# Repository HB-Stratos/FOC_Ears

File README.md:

Hi there! Since the below was written, a few more things have happened:

You can **send me your Email if you want to get involved with development** and I'll reach out. [Click Here](https://app.formbricks.com/s/cmjj02hcw36xmad01dme5074u).

Work has also started on a PCB based version. PCBs have been ordered, and may or may not have arrived in time for Congress. \
In any case, you can find all KiCad files [on the rev2 branch](https://github.com/HB-Stratos/FOC_Ears/tree/rev-2).

# FOC Ears: Dead Silent Animatronics, a Prototype

This repository documents my work to create truly silent animatronic cat ears.

The classic design using RC airplane servos is quite noisy, and I wanted to fix that to build animatronics that you can comfortably hold a conversation around.

## Table of Contents

- [FOC Ears: Dead Silent Animatronics, a Prototype](#foc-ears-dead-silent-animatronics-a-prototype)
  - [Table of Contents](#table-of-contents)
  - [Status](#status)
    - [Future Plans](#future-plans)
  - [Documentation](#documentation)
    - [System Overview](#system-overview)
      - [Components](#components)
      - [Motor Assembly](#motor-assembly)
    - [Wiring](#wiring)
    - [3D Prints and Mounting](#3d-prints-and-mounting)
    - [Build Environment Setup](#build-environment-setup)
    - [Misc. Lessons Learned](#misc-lessons-learned)
  - [Thanks](#thanks)
  - [Finally](#finally)

## Status

I managed to create a working prototype in time for GPN23. It has a rather bulky perfboard electronics package and several electronic design limitations, such as the lack of a fuse, but it held up well for the entire event. Unfortunately, my phone died between building the prototype and writing this documentation, so I have lost some work-in-progress photographs. Words and renders will have to suffice.

<details>
<summary>More Pictures (expand)</summary>

</details>

### Future Plans

I plan to develop a more robust version with a printed circuit board between the ears to house the electronics in a much neater way. I would like to eventually create a product out of this development, but even if I do, I plan to keep all design files and details open source.

## Documentation

> [!IMPORTANT] > **This is a prototype**. I am documenting this for sake of posterity. If you wish to replicate this design, you are welcome to do so. However, expect to face issues, poor design decisions and have expect to solve many stupid problems on your own. Because of this, this is not written as a tutorial, but more as an overview of what it takes. That said, I'm happy to help where I can, just leave an issue on the repo here.

With that said, lets get into it

### System Overview

#### Components

The system consists of the following components:

- An [ESP32WROOM](https://aliexpress.com/item/1005008002597306.html) micro controller <br>

- Two [SimpleFOC mini](https://docs.simplefoc.com/simplefocmini) driver boards <br>

- Two [Mitoot 2208 100kv](https://aliexpress.com/item/1005006008489660.html) Brushless Gimbal Motors <br>

- Two [MT6701qt](https://aliexpress.com/item/1005007349429583.html) Magnetic Encoders <br>

- A [BNO055](https://aliexpress.com/item/1005006770124726.html) IMU <br>

- Ears from Aliexpress. There appears to be a whole range of different style ears on Aliexpress, all following the same basic design. Look for the ears in the ~10€ price class, those will likely be extremely similar to [the ones I used](https://aliexpress.com/item/1005004647818937.html). <br>

- A generic 3.3V Regulator (must be 15V capable)
- A generic configurable USB-C PD trigger board (prototype used 15V)
- A generic USB-C PD capable Power Bank (in my case 100W 20V capable)

Total cost exluding the power bank comes out to ~53€.

Images were taken from their respective linked pages.

> [!NOTE]
> The hardware choices I made worked, but were not ideal:
>
> - The ESP32 can not be flashed without having to hold down the boot button every time
> - The Motors come with the wire through their hub, so one needs to depin the connector, pull the cable through and add the pins again.
> - The Motors are also a bit large, smaller probably works but untested.
> - The Encoder board is undocumented, had to be reverse engineered with the chip data sheet
> - The BNO055 has some hardware issues and is also discontinued, but it was the board I had laying around.

#### Motor Assembly

The motor and encoder are mounted together by a stack of parts that clamps the two to each other and the assembly to the head band using all the same screws. The magnet for the encoder is held within the hollow motor shaft by a press fit 3d printed adapter. The ears are mounted on top with two M2x6 screws through the U channel piece.

Ordinarily this wouldn't work as the holes in the motor do not match the holes in the encoder PCB. However there is nothing vital in the ares of the encoder PCB where the holes are needed, so I devised a 3d printed drilling jig to create the required holes. Of course this technique is only applicable to the exact sensor board I used.

> [!CAUTION]
> Using too long screws to clamp the motor-encoder assembly together will destroy the motor. The holes do not have a backstop, so you will penetrate the coils with the screw. You will not feel rotational resistance as this happens as you are only hitting the stator. I used M2.5x8 screws.

The ears are mounted by making a cutout in them with flush cutters to fit the U channel piece, which is then glued into place with super glue. It is vital that this cut is deeper than the u channel such that the outer edges of the ear sit as flush as possible to the head band. The U channel does not extend all the way down as it would snag on the motor cables if it did.

Additionally, for secondary motion the lower ear lobe of each ear is mounted to a slider on the head band. This causes the ear to fold on rotation, which looks much more natural than the long ear lobe swinging backwards. This however has the issue that the aliexpress ears come with thick wire in them for posing, which would prevent this motion. The solution is as simple as it is ugly: fatigue cracking the wire every 5 or so mm with pliers within the area that should bend. The slider is printed from TPU for silent motion and (surprisingly) low friction.

> [!NOTE]
> I have tried to completely remove the wire from the ears. The wire is hot glued in place within the ears in multiple places, and the fur is bonded together firmly. Even by cutting along the edge of the ear all the way around I was not able to extract the wire in the base of the ear, and said cut looked quite ugly and would have been hard to close up again. Hence I deemed it better to leave the wire in place, but fatigue crack it where necessary. A less hand-fatiguing solution is definitely needed for higher volume production though.

The ear detached from the motor, with lines highlighting roughly where I broke the internal wire. Also visible is the TPU slider, here detached from the rail.

### Wiring

PowerPoint graphic design is my passion. Not pictured are 3.3v running to all sensors, shared ground between all and a 2.2k pullup resistor between SDA and 3.3V on the BNO055. Additionally, note that I used SimpleFOC Mini 1.0 driver boards as they were easily available on Aliexpress. SimpleFOC Mini 1.1 drivers are similar, but their pin order appears to be flipped.

Here's the reverse-engineered diagram for the encoder. Also, [here's the datasheet](https://uploadcdn.oneyac.com/attachments/files/brand_pdf/magntek/F3/CA/MT6701QT-STD.pdf).

> [!NOTE]
> This encoder is supposedly capable of I2C and SSI (we use SSI), and CS would toggle between the two modes. However this would cause bad I2C writes on the shared SSI bus with CS off, which I have heard reported, but could never observe myself. I can only assume my specific board has some resistors onboard that disable I2C.

A closeup of the final breadboard. Unsurprisingly, gluing circuit boards together edge to edge did not prove to be particularly sturdy, and the design made the USB-C cable start uncomftably low. But it did work.

### 3D Prints and Mounting

This is the mount for the board, based of my earlier design of ear hook glasses clips to mount non-animatronic ears. This glasses clip is desiged for my glasses (Zenni Optical [Navy Rectangle Glasses #2018916](https://www.zennioptical.com/p/tr-rectangle-eyeglass-frames/20189/2018916) ), so if these do not also happen to be your glasses you will have to devise a custom mounting solution. I am yet to come up with a generic solution that would work with all glasses while still looking good.

Also, this piece is a royal pain to print as one might expect. The first print of it I did completed, but all five attempts to print a spare piece before the event failed.

The parts constituting one motor-encoder-ear sandwich, laid out in the orientation I printed them in.

The ear lobe slider which glides on the metal headband. It is printed from TPU for silent motion. Earlier prototypes showed that even the slightest bit of noise so close to the wearer's ear is quite annoying.

All 3d printed parts can be found in the `printed_parts` directory as STEP files, as well as the original Fusion360 source files. Do note however that the source files are a royal mess as they were created during prototyping and with exactly zero patience.

### Build Environment Setup

This project uses PlatformIO instead of the Arduino IDE as it has far superior code completion and extension support. Setting up the build environment should just be as easy as setting up PlatformIO using the [official guide](https://docs.platformio.org/en/latest/integration/ide/vscode.html#quick-start) and cloning this repository into the workspace. It will take a few minutes to load, but PlatformIO should automatically download all required frameworks and libraries as specified in the `platformio.ini` file. If this doesn't work for whatever reason, please do open an issue. Also, for some reason this was removed from the official settings, but PlatformIO does offer an "Upload and Monitor (connect to Serial Monitor immediately)" mode. You can find out how to set this up [here](https://community.platformio.org/t/shortcut-to-upload-and-monitor-task-while-also-restarting-it-if-active/18104/5).

### Misc. Lessons Learned

- If the screws clamping the encoder to the motor are not tight enough, the motor likes to shake itself to bits as it twisting against the encoder causes a feedback loop.
- If the screws clamping the encoder to the motor are too tight, they can stretch a poorly printed plastic clamp and make the mounting screws penetrate the motor core.
- Having a cheap oscilloscope ([Zoyi ZT-703S](https://aliexpress.com/item/1005006593085723.html), ~80€) was invaluable during development, you likely want one too.
- At least on my BNO055 board the I2C pullups were too weak for high frequencies, an external pullup was needed.
- Having a Dupont connector crimping tool is quite useful.
- Surprisingly, the mess of wires going from the sensors and motors to the perfboard never got tangled. Still, they're a bad design.
- Having any D term in the PID motion controllers makes the motor quite noisy.
- High loop speed of the main FOC loop is important for precise and silent control.
- Any change in loop speed also constitutes a change in optimal PID values, a fixed loop speed would be a good code design choice I did not make.
- A RP2040 has pretty low loop speed due to lack of a hardware floating point unit, not ideal for this application.
- Many in and output pins are needed to control the motors, 4 per motor driver, one per sensor plus two more sensor shared pins, plus the I2C pins for the IMU. I almost ran out of useable IO pins on the ESP32.
- Reading the IMU every loop slows the motor control loop down too much, reading the IMU every 10 ms was found to be sufficient.
- A PT1 filter element was integrated into the motor driver to limit maximum acceleration, safeguarding from a position step input being too violent.
- The clamping pieces should be printed from ASA or similar, especially during testing or with a sensor error, the motors can get quite hot.
- The metal hoop that comes with the aliexpress cat ears is bent outwards at the bottom. Bending it straight makes sliding mounts with much tighter tolerances on possible.
- Fatigue cracking the ears works, but likes to compress the fur under the pliers. Scratching it with finger nails appears to restore most of the fluff.
- Mounting the ears to my glasses proved essential. The motors are not the lightest, and with my mounting solution clipping onto my glasses and hooking behind my ears, I never feared losing the ears. I am yet to come up with a solution that would work for all glasses frames, let alone a solution for people who do not wear glasses.
- Espressif changed something in more recent versions of the framework, which broke SimpleFOC. It either doesn't compile or kernel panics. I went and found the newest version released before the latest SFOC release, which worked well. You can find the details in the platformio.ini file.
- SimpleFOC requires that PlatformIO `lib_archive = false`. If it isn't your code will compile and run, but behave weirdly in all sorts of strange ways. Be careful.
- The Motors claim they can handle 12V, but I have driven them to 20V with no issues. I just went with 15V as I didn't need the torque and it slowed the motor heating up should an ear become blocked.
- This project started with me trying to use silent stepper drivers and motors for the motion instead of FOC. However, the holding current being constantly drawn by the stepper motors made them get very hot while still lacking torque to not miss steps. Still, using TMC2209 stepper drivers might work for smaller animatronics such as blinking eyes.
- If you can't upload the code with error Access Denied, check if you have a 3D printer slicer such as Cura open. It was automatically trying to connect to all COM ports for me, blocking code uploads.

## Thanks

to everyone who helped me with this project. Especially the amazing people of the Voidstarlab and SimpleFOC discord who took their time to not only help me debug problems with my motor setup, but also with reverse engineering the Encoder PCB, debugging the IMU and many other hardware engineering issues unrelated to SFOC. This was my first true hardware engineering project. I learned a ton, and I couldn't have done it without y'all.

## Finally

Overengineer more silly projects, build cool stuff, and have fun!

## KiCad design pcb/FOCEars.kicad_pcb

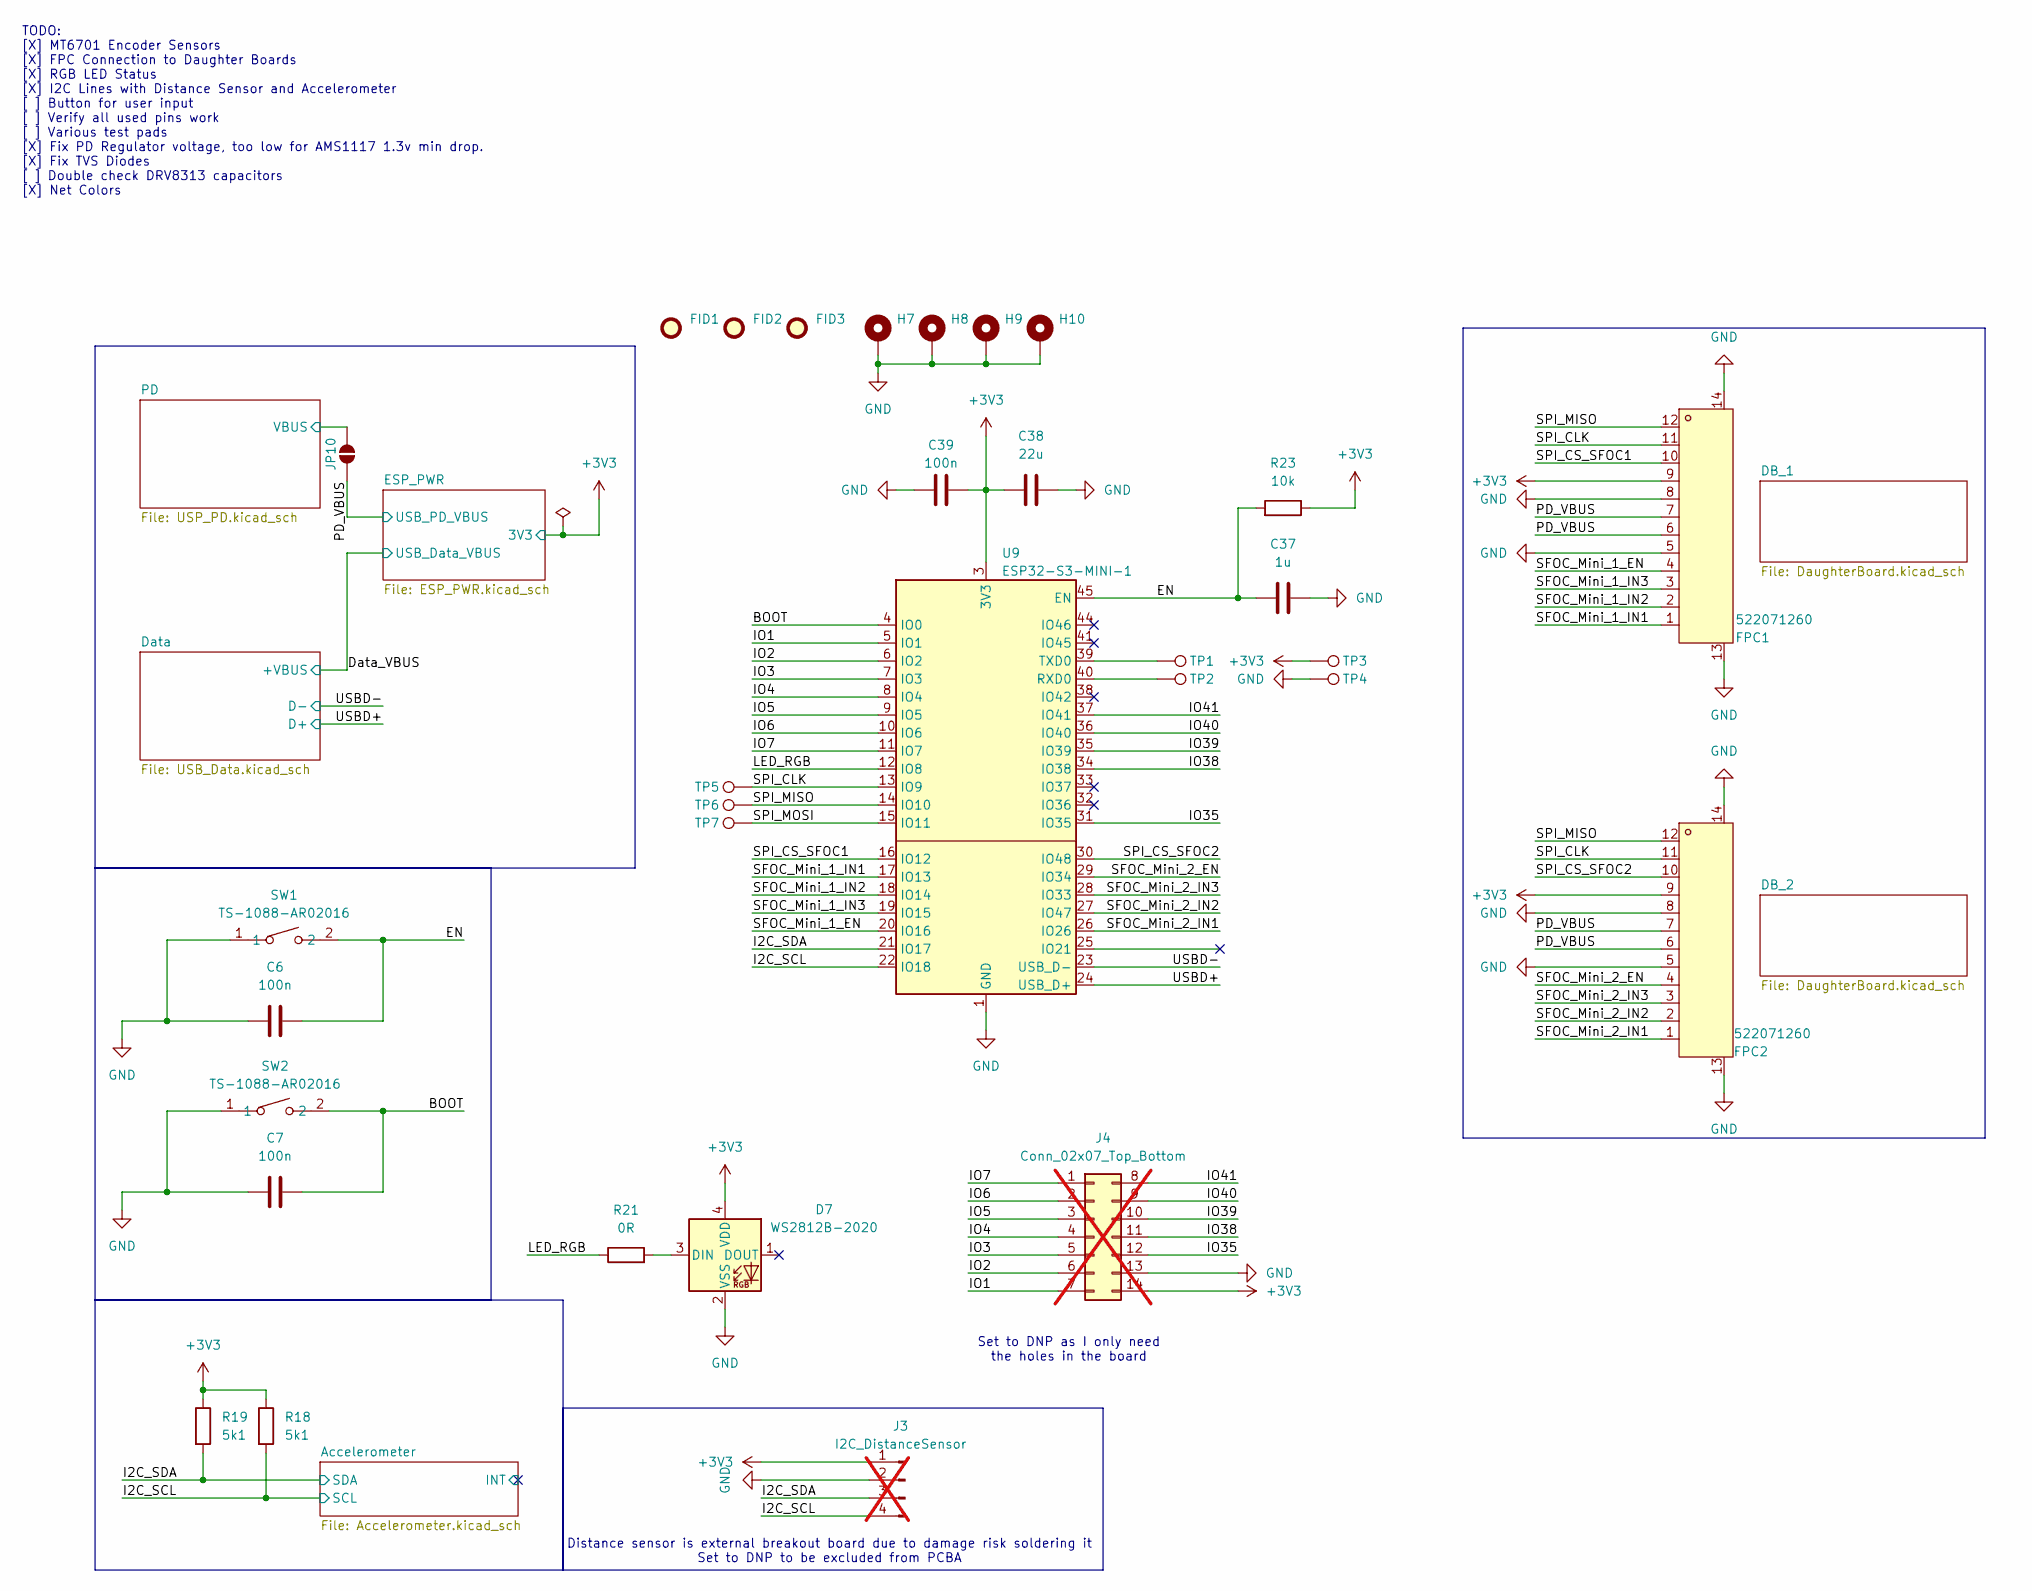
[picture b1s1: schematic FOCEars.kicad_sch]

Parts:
C6, C7, C39: 100n; C_0402_1005Metric; LCSC Part C307331
C37: 1u; C_0402_1005Metric; LCSC Part C52923
C38: 22u; C_0805_2012Metric; LCSC Part C45783
D7: WS2812B-2020; LED_WS2812B-2020_PLCC4_2.0x2.0mm; LCSC Part C965555
FID1, FID2, FID3: Fiducial; Fiducial_1mm_Mask2mm
FPC1, FPC2: 522071260; CONN-SMD_522071260; LCSC Part C565052
H7, H8, H9, H10: MountingHole_Pad; MountingHole_2.2mm_M2_DIN965_Pad_TopBottom
J3: I2C_DistanceSensor; PinHeader_1x04_P2.54mm_Vertical; not fitted
J4: Conn_02x07_Top_Bottom; PinHeader_2x07_P2.54mm_Vertical; not fitted
JP10: SolderJumper_2_Open; SolderJumper-2_P1.3mm_Open_TrianglePad1.0x1.5mm
R18, R19: 5k1; R_0402_1005Metric; LCSC Part C25905
R21: 0R; R_0603_1608Metric; LCSC Part C21189
R23: 10k; R_0402_1005Metric; LCSC Part C25744
SW1, SW2: TS-1088-AR02016; SW-SMD_L3.9-W3.0-P4.45; LCSC Part C720477
TP1, TP2, TP3, TP4, TP5, TP6, TP7: TestPoint; TestPoint_Pad_D1.0mm
U9: ESP32-S3-MINI-1; ESP32-S2-MINI-1; LCSC Part C2913206

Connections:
+3V3: C38.1, C39.2, D7.4 (VDD), FPC1.9, FPC2.9, J3.1, J4.14, R18.1, R19.1, R23.1, TP3.1, U9.3 (3V3); also elsewhere on the board
/BOOT: C7.2, SW2.2, U9.4 (IO0)
/EN: C6.2, C37.2, R23.2, SW1.2, U9.45 (EN)
/I2C_SCL: J3.4, R18.2, U9.22 (IO18); also elsewhere on the board
/I2C_SDA: J3.3, R19.2, U9.21 (IO17); also elsewhere on the board
/IO1: J4.7, U9.5 (IO1)
/IO2: J4.6, U9.6 (IO2)
/IO3: J4.5, U9.7 (IO3)
/IO4: J4.4, U9.8 (IO4)
/IO5: J4.3, U9.9 (IO5)
/IO6: J4.2, U9.10 (IO6)
/IO7: J4.1, U9.11 (IO7)
/IO35: J4.12, U9.31 (IO35)
/IO38: J4.11, U9.34 (IO38)
/IO39: J4.10, U9.35 (IO39)
/IO40: J4.9, U9.36 (IO40)
/IO41: J4.8, U9.37 (IO41)
/LED_RGB: R21.1, U9.12 (IO8)
/PD/VBUS: JP10.2 (B); also elsewhere on the board
/PD_VBUS: FPC1.6, FPC1.7, FPC2.6, FPC2.7, JP10.1 (A); also elsewhere on the board
/SFOC_Mini_1_EN: FPC1.4, U9.20 (IO16)
/SFOC_Mini_1_IN1: FPC1.1, U9.17 (IO13)
/SFOC_Mini_1_IN2: FPC1.2, U9.18 (IO14)
/SFOC_Mini_1_IN3: FPC1.3, U9.19 (IO15)
/SFOC_Mini_2_EN: FPC2.4, U9.29 (IO34)
/SFOC_Mini_2_IN1: FPC2.1, U9.26 (IO26)
/SFOC_Mini_2_IN2: FPC2.2, U9.27 (IO47)
/SFOC_Mini_2_IN3: FPC2.3, U9.28 (IO33)
/SPI_CLK: FPC1.11, FPC2.11, TP5.1, U9.13 (IO9)
/SPI_CS_SFOC1: FPC1.10, U9.16 (IO12)
/SPI_CS_SFOC2: FPC2.10, U9.30 (IO48)
/SPI_MISO: FPC1.12, FPC2.12, TP6.1, U9.14 (IO10)
/SPI_MOSI: TP7.1, U9.15 (IO11)
/USBD+: U9.24 (USB_D+); also elsewhere on the board
/USBD-: U9.23 (USB_D-); also elsewhere on the board
GND: C6.1, C7.1, C37.1, C38.2, C39.1, D7.2 (VSS), FPC1.5, FPC1.8, FPC1.13, FPC1.14, FPC2.5, FPC2.8, FPC2.13, FPC2.14, H7.1, H8.1, H9.1, H10.1, J3.2, J4.13, SW1.1, SW2.1, TP4.1, U9.1 (GND), U9.2 (GND), U9.42 (GND), U9.43 (GND), U9.46 (GND), U9.47 (GND), U9.48 (GND), U9.49 (GND), U9.50 (GND), U9.51 (GND), U9.52 (GND), U9.53 (GND), U9.54 (GND), U9.55 (GND), U9.56 (GND), U9.57 (GND), U9.58 (GND), U9.59 (GND), U9.60 (GND), U9.61 (GND), U9.62 (GND), U9.63 (GND), U9.64 (GND), U9.65 (GND); also elsewhere on the board
unnamed: D7.3 (DIN), R21.2
unnamed: TP2.1, U9.40 (RXD0)
unnamed: TP1.1, U9.39 (TXD0)

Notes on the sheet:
TODO: [X] MT6701 Encoder Sensors [X] FPC Connection to Daughter Boards [X] RGB LED Status [X] I2C Lines with Distance Sensor and Accelerometer [ ] Button for user input [ ] Verify all used pins work [ ] Various test pads [X] Fix PD Regulator voltage, too low for AMS1117 1.3v min drop. [X] Fix TVS D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
Set to DNP as I only need the holes in the board
Distance sensor is external breakout board due to damage risk soldering it Set to DNP to be excluded from PCBA

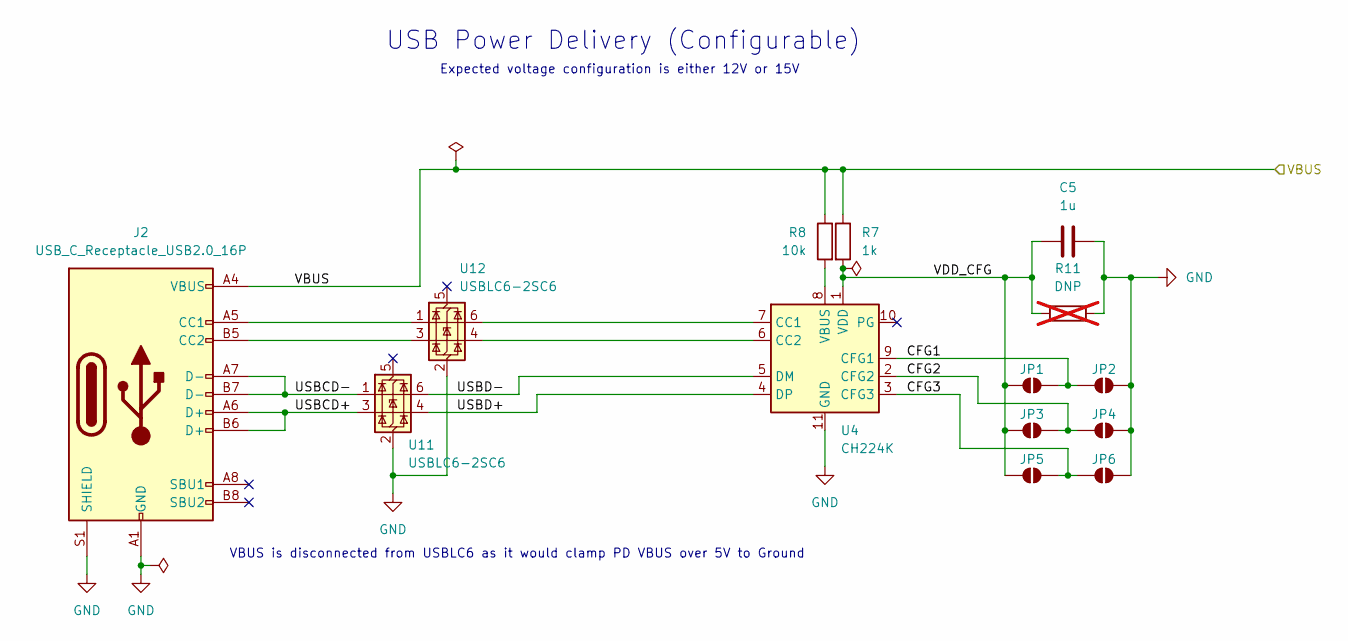
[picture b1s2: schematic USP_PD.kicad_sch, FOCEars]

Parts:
C5: 1u; C_0402_1005Metric; LCSC Part C52923
J2: USB_C_Receptacle_USB2.0_16P; USB_C_Receptacle_GCT_USB4105-xx-A_16P_TopMnt_Horizontal; LCSC Part C5184243
JP1, JP2, JP3, JP4, JP5, JP6: SolderJumper_2_Open; SolderJumper-2_P1.3mm_Open_TrianglePad1.0x1.5mm
R7: 1k; R_0402_1005Metric; LCSC Part C11702
R8: 10k; R_0402_1005Metric; LCSC Part C25744
R11: DNP; R_0402_1005Metric; not fitted
U4: CH224K; SSOP-10-1EP_3.9x4.9mm_P1mm_EP2.1x3.3mm; LCSC Part C970725
U11, U12: USBLC6-2SC6; SOT-23-6; LCSC Part C7519

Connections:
/PD/CFG1: JP1.2 (B), JP2.1 (A), U4.9 (CFG1)
/PD/CFG2: JP3.2 (B), JP4.1 (A), U4.2 (CFG2)
/PD/CFG3: JP5.2 (B), JP6.1 (A), U4.3 (CFG3)
/PD/USBCD+: J2.A6 (D+), J2.B6 (D+), U11.3 (I/O2)
/PD/USBCD-: J2.A7 (D-), J2.B7 (D-), U11.1 (I/O1)
/PD/USBD+: U4.4 (DP), U11.4 (I/O2)
/PD/USBD-: U4.5 (DM), U11.6 (I/O1)
/PD/VBUS: J2.A4 (VBUS), J2.A9 (VBUS), J2.B4 (VBUS), J2.B9 (VBUS), R7.1, R8.1; also elsewhere on the board
/PD/VDD_CFG: C5.1, JP1.1 (A), JP3.1 (A), JP5.1 (A), R7.2, R11.1, U4.1 (VDD)
GND: C5.2, J2.A1 (GND), J2.A12 (GND), J2.B1 (GND), J2.B12 (GND), J2.S1 (SHIELD), JP2.2 (B), JP4.2 (B), JP6.2 (B), R11.2, U4.11 (GND), U11.2 (GND), U12.2 (GND); also elsewhere on the board
unnamed: J2.A5 (CC1), U12.1 (I/O1)
unnamed: J2.B5 (CC2), U12.3 (I/O2)
unnamed: U4.7 (CC1), U12.6 (I/O1)
unnamed: U4.6 (CC2), U12.4 (I/O2)
unnamed: R8.2, U4.8 (VBUS)

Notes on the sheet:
VBUS is disconnected from USBLC6 as it would clamp PD VBUS over 5V to Ground
USB Power Delivery (Configurable)
Expected voltage configuration is either 12V or 15V

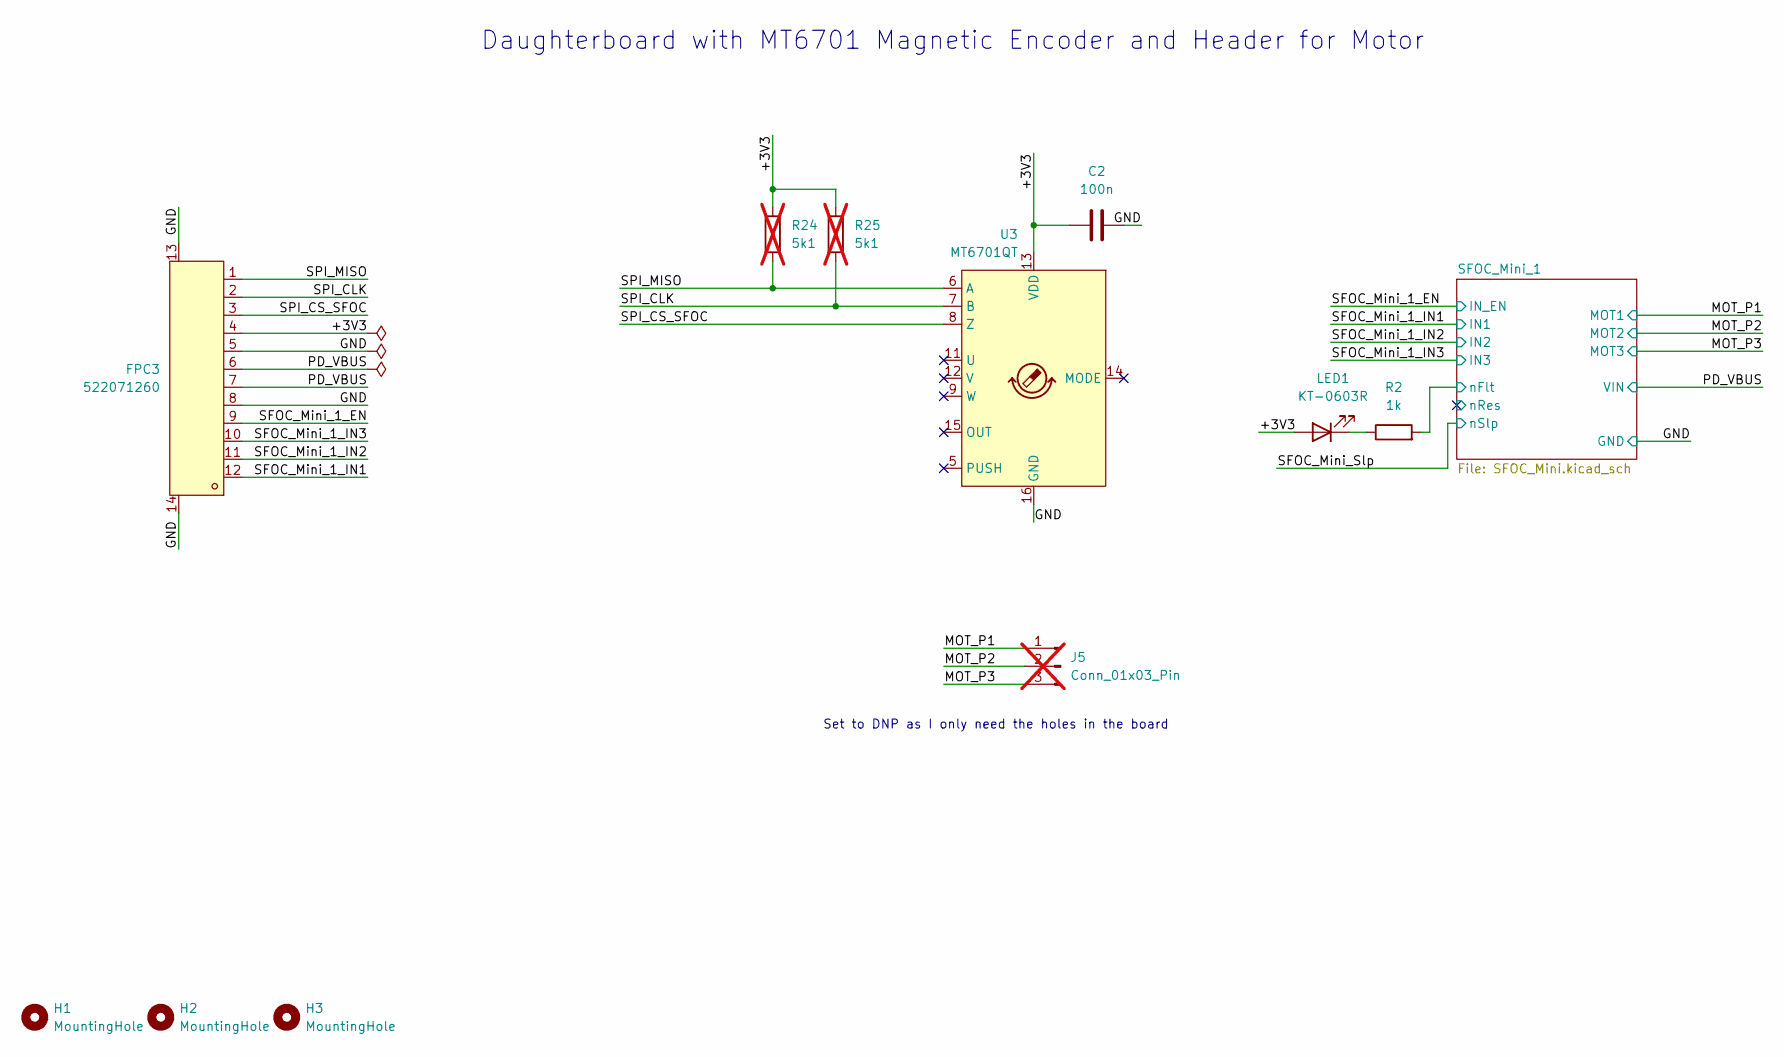
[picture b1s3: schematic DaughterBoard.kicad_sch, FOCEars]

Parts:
C2: 100n; C_0402_1005Metric; LCSC Part C307331
FPC3: 522071260; CONN-SMD_522071260; LCSC Part C565052
H1, H2, H3: MountingHole; MountingHole_2.2mm_M2
J5: Conn_01x03_Pin; PinHeader_1x03_P2.54mm_Vertical; not fitted
LED1: KT-0603R; LED0603-RD; LCSC Part C2286
R2: 1k; R_0402_1005Metric; LCSC Part C11702
R24, R25: 5k1; R_0603_1608Metric; not fitted
U3: MT6701QT; QFN-16-1EP_3x3mm_P0.5mm_EP1.7x1.7mm; LCSC Part C2913974

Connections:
/DB_1/+3V3: C2.2, FPC3.4, LED1.2 (A), R24.1, R25.1, U3.13 (VDD)
/DB_1/GND: C2.1, FPC3.5, FPC3.8, FPC3.13, FPC3.14, U3.16 (GND), U3.17 (GND); also elsewhere on the board
/DB_1/MOT_P1: J5.1; also elsewhere on the board
/DB_1/MOT_P2: J5.2; also elsewhere on the board
/DB_1/MOT_P3: J5.3; also elsewhere on the board
/DB_1/PD_VBUS: FPC3.6, FPC3.7; also elsewhere on the board
/DB_1/SFOC_Mini_1/nFlt: R2.2; also elsewhere on the board
/DB_1/SFOC_Mini_1_EN: FPC3.9; also elsewhere on the board
/DB_1/SFOC_Mini_1_IN1: FPC3.12; also elsewhere on the board
/DB_1/SFOC_Mini_1_IN2: FPC3.11; also elsewhere on the board
/DB_1/SFOC_Mini_1_IN3: FPC3.10; also elsewhere on the board
/DB_1/SPI_CLK: FPC3.2, R25.2, U3.7 (B)
/DB_1/SPI_CS_SFOC: FPC3.3, U3.8 (Z)
/DB_1/SPI_MISO: FPC3.1, R24.2, U3.6 (A)
unnamed: LED1.1 (K), R2.1

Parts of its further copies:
C19: 100n; C_0402_1005Metric; LCSC Part C307331
FPC4: 522071260; CONN-SMD_522071260; LCSC Part C565052
H4, H5, H6: MountingHole; MountingHole_2.2mm_M2
J6: Conn_01x03_Pin; PinHeader_1x03_P2.54mm_Vertical; not fitted
LED2: KT-0603R; LED0603-RD; LCSC Part C2286
R14: 1k; R_0402_1005Metric; LCSC Part C11702
R26, R27: 5k1; R_0603_1608Metric; not fitted
U8: MT6701QT; QFN-16-1EP_3x3mm_P0.5mm_EP1.7x1.7mm; LCSC Part C2913974

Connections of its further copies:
/DB_2/+3V3: C19.2, FPC4.4, LED2.2 (A), R26.1, R27.1, U8.13 (VDD)
/DB_2/GND: C19.1, FPC4.5, FPC4.8, FPC4.13, FPC4.14, U8.16 (GND), U8.17 (GND); also elsewhere on the board
/DB_2/MOT_P1: J6.1; also elsewhere on the board
/DB_2/MOT_P2: J6.2; also elsewhere on the board
/DB_2/MOT_P3: J6.3; also elsewhere on the board
/DB_2/PD_VBUS: FPC4.6, FPC4.7; also elsewhere on the board
/DB_2/SFOC_Mini_1/nFlt: R14.2; also elsewhere on the board
/DB_2/SFOC_Mini_1_EN: FPC4.9; also elsewhere on the board
/DB_2/SFOC_Mini_1_IN1: FPC4.12; also elsewhere on the board
/DB_2/SFOC_Mini_1_IN2: FPC4.11; also elsewhere on the board
/DB_2/SFOC_Mini_1_IN3: FPC4.10; also elsewhere on the board
/DB_2/SPI_CLK: FPC4.2, R27.2, U8.7 (B)
/DB_2/SPI_CS_SFOC: FPC4.3, U8.8 (Z)
/DB_2/SPI_MISO: FPC4.1, R26.2, U8.6 (A)
unnamed: LED2.1 (K), R14.1

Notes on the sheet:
Set to DNP as I only need the holes in the board
Daughterboard with MT6701 Magnetic Encoder and Header for Motor

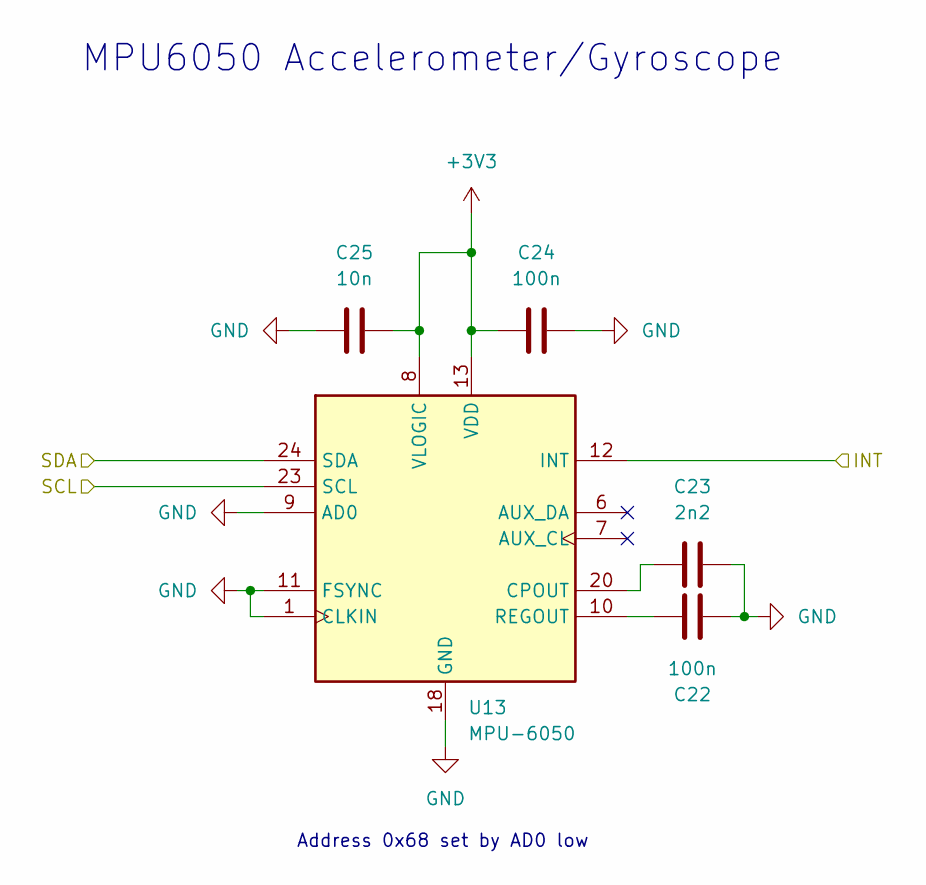
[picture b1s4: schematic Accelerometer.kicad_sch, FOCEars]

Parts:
C22, C24: 100n; C_0402_1005Metric; LCSC Part C307331
C23: 2n2; C_0603_1608Metric; LCSC Part C1604
C25: 10n; C_0402_1005Metric; LCSC Part C15195
U13: MPU-6050; InvenSense_QFN-24_4x4mm_P0.5mm; LCSC Part C24112

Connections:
+3V3: C24.1, C25.2, U13.8 (VLOGIC), U13.13 (VDD); also elsewhere on the board
/Accelerometer/INT: U13.12 (INT)
/I2C_SCL: U13.23 (SCL); also elsewhere on the board
/I2C_SDA: U13.24 (SDA); also elsewhere on the board
GND: C22.2, C23.2, C24.2, C25.1, U13.1 (CLKIN), U13.9 (AD0), U13.11 (FSYNC), U13.18 (GND); also elsewhere on the board
unnamed: C23.1, U13.20 (CPOUT)
unnamed: C22.1, U13.10 (REGOUT)

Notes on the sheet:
MPU6050 Accelerometer/Gyroscope
Address 0x68 set by AD0 low

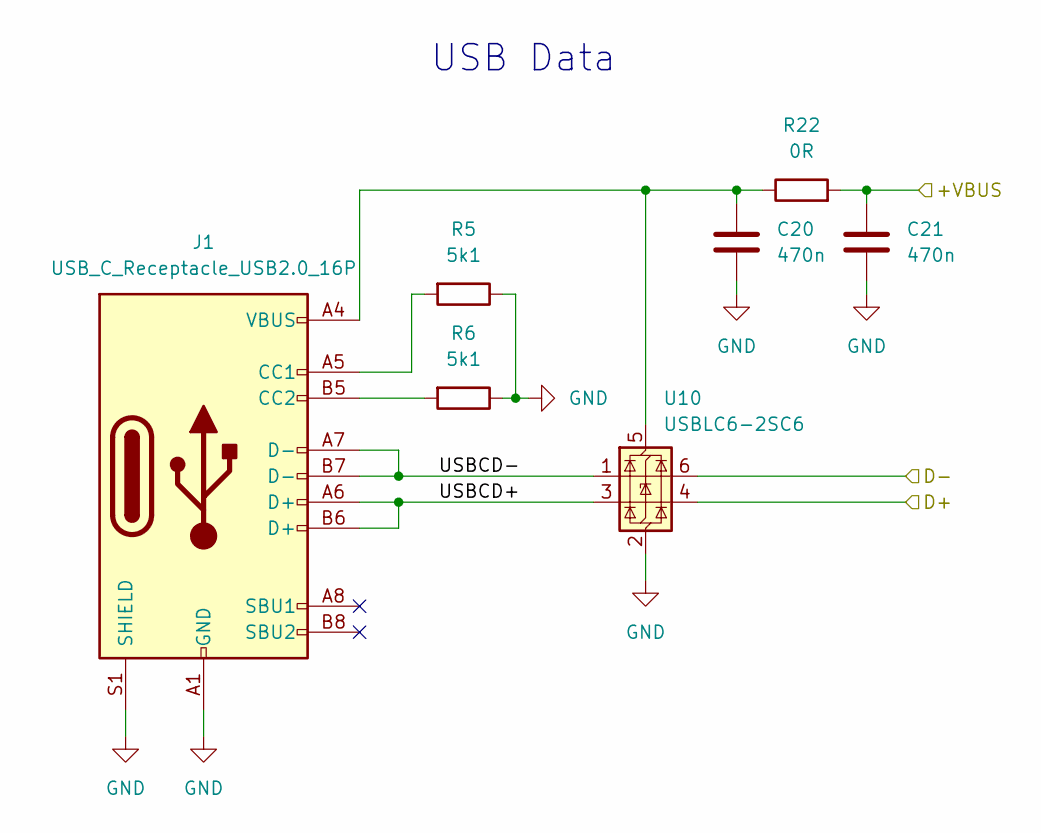
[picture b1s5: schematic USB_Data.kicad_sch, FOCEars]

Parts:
C20, C21: 470n; C_0603_1608Metric; LCSC Part C1623
J1: USB_C_Receptacle_USB2.0_16P; USB_C_Receptacle_GCT_USB4105-xx-A_16P_TopMnt_Horizontal; LCSC Part C5184243
R5, R6: 5k1; R_0402_1005Metric; LCSC Part C25905
R22: 0R; R_0603_1608Metric; LCSC Part C21189
U10: USBLC6-2SC6; SOT-23-6; LCSC Part C7519

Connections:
/Data/USBCD+: J1.A6 (D+), J1.B6 (D+), U10.3 (I/O2)
/Data/USBCD-: J1.A7 (D-), J1.B7 (D-), U10.1 (I/O1)
/Data_VBUS: C21.2, R22.2; also elsewhere on the board
/USBD+: U10.4 (I/O2); also elsewhere on the board
/USBD-: U10.6 (I/O1); also elsewhere on the board
GND: C20.1, C21.1, J1.A1 (GND), J1.A12 (GND), J1.B1 (GND), J1.B12 (GND), J1.S1 (SHIELD), R5.1, R6.1, U10.2 (GND); also elsewhere on the board
unnamed: J1.A5 (CC1), R5.2
unnamed: J1.B5 (CC2), R6.2
unnamed: C20.2, J1.A4 (VBUS), J1.A9 (VBUS), J1.B4 (VBUS), J1.B9 (VBUS), R22.1, U10.5 (VBUS)

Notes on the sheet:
USB Data

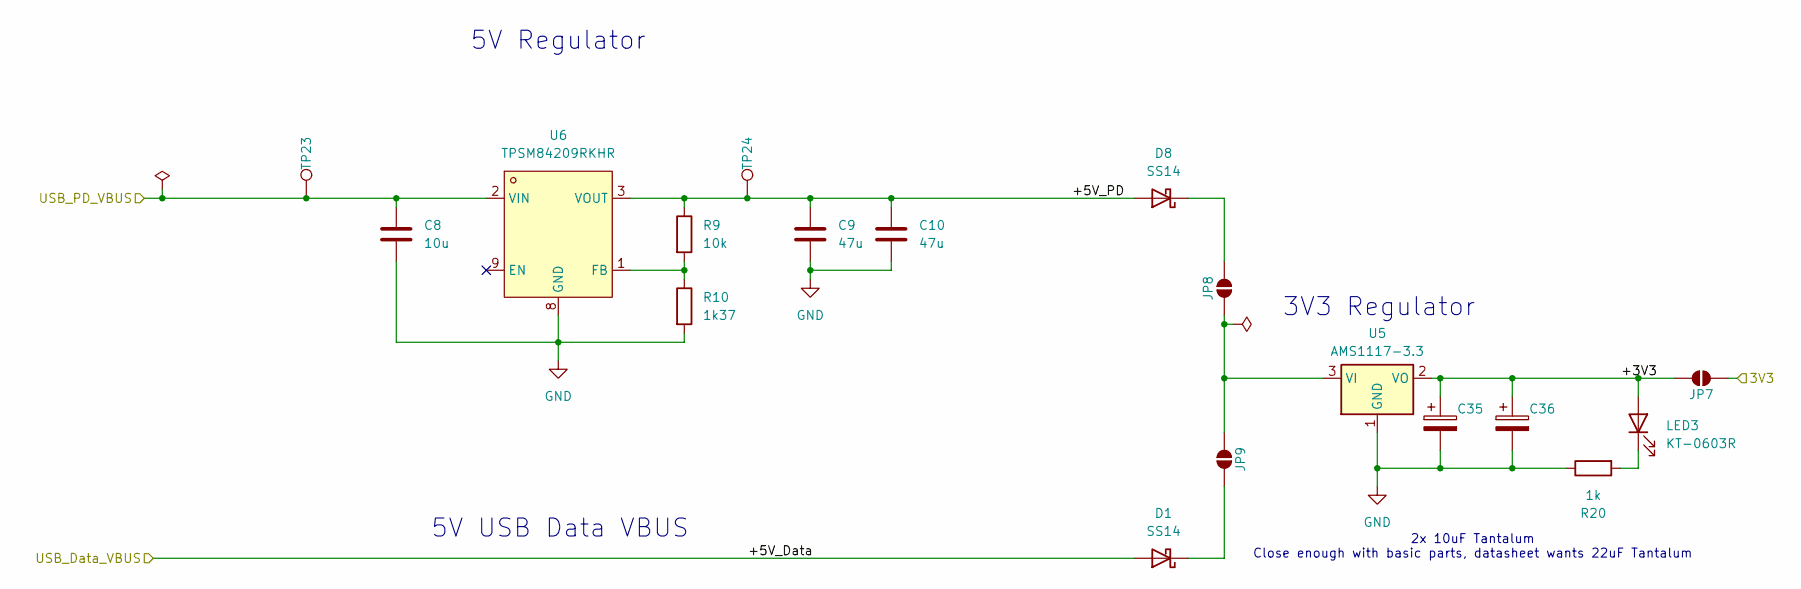
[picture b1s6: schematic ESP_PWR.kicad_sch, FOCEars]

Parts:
C8: 10u; C_1206_3216Metric; LCSC Part C13585
C9, C10: 47u; C_1206_3216Metric; LCSC Part C96123
C35, C36: TAJA106K016RNJ; CAP-SMD_L3.2-W1.6-RD-C7171; LCSC Part C7171
D1, D8: SS14; D_SMA; LCSC Part C2480
JP7, JP8, JP9: SolderJumper_2_Open; SolderJumper-2_P1.3mm_Open_TrianglePad1.0x1.5mm
LED3: KT-0603R; LED0603-RD; LCSC Part C2286
R9: 10k; R_0402_1005Metric; LCSC Part C25744
R10: 1k37; R_0402_1005Metric; LCSC Part C159124
R20: 1k; R_0402_1005Metric; LCSC Part C11702
TP23, TP24: TestPoint; TestPoint_Pad_D1.0mm
U5: AMS1117-3.3; SOT-223-3_TabPin2; LCSC Part C6186
U6: TPSM84209RKHR; QFN-9_L4.5-W4.0_TPSM84209RKHR; LCSC Part C2878926

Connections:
+3V3: JP7.1 (A); also elsewhere on the board
/Data_VBUS: D1.2 (A); also elsewhere on the board
/ESP_PWR/+3V3: C35.1, C36.1, JP7.2 (B), LED3.2 (A), U5.2 (VO)
/ESP_PWR/+5V_PD: C9.1, C10.1, D8.2 (A), R9.1, TP24.1, U6.3 (VOUT)
/PD_VBUS: C8.1, TP23.1, U6.2 (VIN); also elsewhere on the board
GND: C8.2, C9.2, C10.2, C35.2, C36.2, R10.2, R20.1, U5.1 (GND), U6.8 (GND); also elsewhere on the board
unnamed: D1.1 (K), JP9.2 (B)
unnamed: D8.1 (K), JP8.2 (B)
unnamed: JP8.1 (A), JP9.1 (A), U5.3 (VI)
unnamed: LED3.1 (K), R20.2
unnamed: R9.2, R10.1, U6.1 (FB)

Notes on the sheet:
5V USB Data VBUS
2x 10uF Tantalum Close enough with basic parts, datasheet wants 22uF Tantalum
3V3 Regulator
5V Regulator

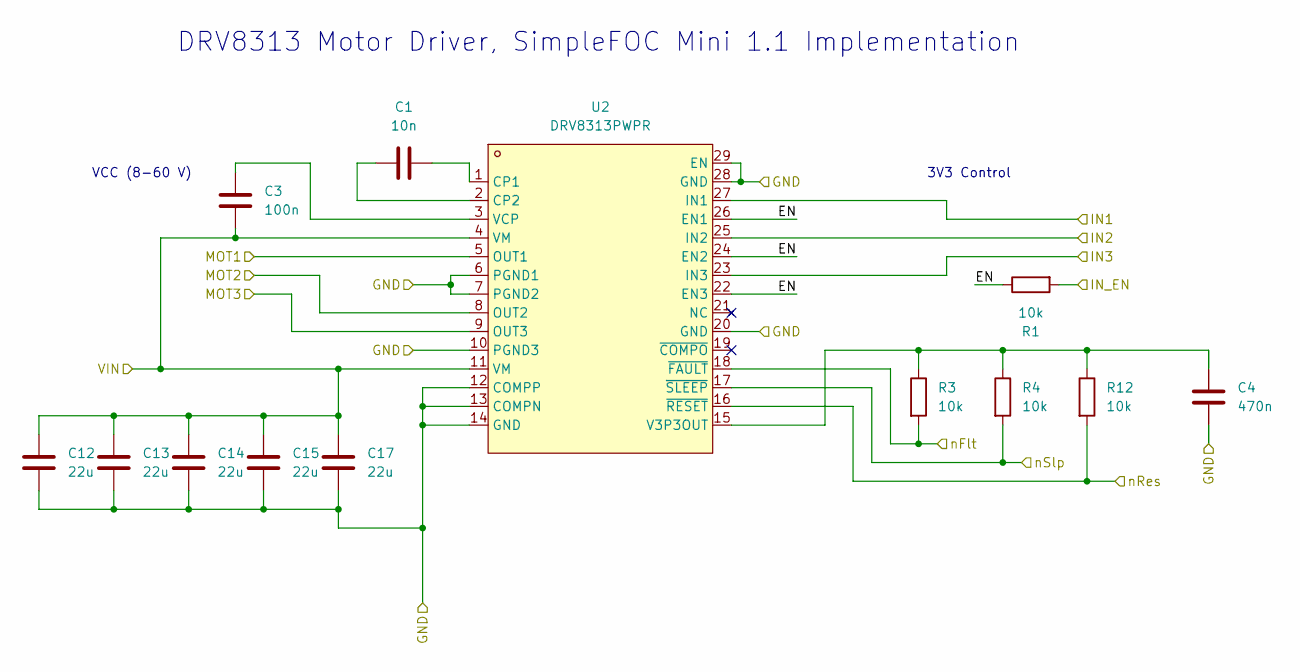
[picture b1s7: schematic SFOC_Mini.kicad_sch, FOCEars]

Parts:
C1: 10n; C_0402_1005Metric; LCSC Part C15195
C3: 100n; C_0402_1005Metric; LCSC Part C307331
C4: 470n; C_0603_1608Metric; LCSC Part C1623
C12, C13, C14, C15, C17: 22u; C_0805_2012Metric; LCSC Part C45783
R1, R3, R4, R12: 10k; R_0402_1005Metric; LCSC Part C25744
U2: DRV8313PWPR; HTSSOP-28_L9.8-W4.5-P0.65-LS6.6-BL-EP; LCSC Part C92482

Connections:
/DB_1/GND: C4.1, C12.2, C13.2, C14.2, C15.2, C17.2, U2.6 (PGND1), U2.7 (PGND2), U2.10 (PGND3), U2.12 (COMPP), U2.13 (COMPN), U2.14 (GND), U2.20 (GND), U2.28 (GND), U2.29 (EN); also elsewhere on the board
/DB_1/MOT_P1: U2.5 (OUT1); also elsewhere on the board
/DB_1/MOT_P2: U2.8 (OUT2); also elsewhere on the board
/DB_1/MOT_P3: U2.9 (OUT3); also elsewhere on the board
/DB_1/PD_VBUS: C3.1, C12.1, C13.1, C14.1, C15.1, C17.1, U2.4 (VM), U2.11 (VM); also elsewhere on the board
/DB_1/SFOC_Mini_1/EN: R1.1, U2.22 (EN3), U2.24 (EN2), U2.26 (EN1)
/DB_1/SFOC_Mini_1/nFlt: R3.2, U2.18 (~FAULT); also elsewhere on the board
/DB_1/SFOC_Mini_1/nRes: R12.2, U2.16 (~RESET)
/DB_1/SFOC_Mini_1_EN: R1.2; also elsewhere on the board
/DB_1/SFOC_Mini_1_IN1: U2.27 (IN1); also elsewhere on the board
/DB_1/SFOC_Mini_1_IN2: U2.25 (IN2); also elsewhere on the board
/DB_1/SFOC_Mini_1_IN3: U2.23 (IN3); also elsewhere on the board
/DB_1/SFOC_Mini_Slp: R4.2, U2.17 (~SLEEP)
unnamed: C1.2, U2.1 (CP1)
unnamed: C1.1, U2.2 (CP2)
unnamed: C4.2, R3.1, R4.1, R12.1, U2.15 (V3P3OUT)
unnamed: C3.2, U2.3 (VCP)

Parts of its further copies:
C18: 10n; C_0402_1005Metric; LCSC Part C15195
C26: 100n; C_0402_1005Metric; LCSC Part C307331
C27: 470n; C_0603_1608Metric; LCSC Part C1623
C28, C29, C30, C31, C32: 22u; C_0805_2012Metric; LCSC Part C45783
R13, R15, R16, R17: 10k; R_0402_1005Metric; LCSC Part C25744
U7: DRV8313PWPR; HTSSOP-28_L9.8-W4.5-P0.65-LS6.6-BL-EP; LCSC Part C92482

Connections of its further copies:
/DB_2/GND: C27.1, C28.2, C29.2, C30.2, C31.2, C32.2, U7.6 (PGND1), U7.7 (PGND2), U7.10 (PGND3), U7.12 (COMPP), U7.13 (COMPN), U7.14 (GND), U7.20 (GND), U7.28 (GND), U7.29 (EN); also elsewhere on the board
/DB_2/MOT_P1: U7.5 (OUT1); also elsewhere on the board
/DB_2/MOT_P2: U7.8 (OUT2); also elsewhere on the board
/DB_2/MOT_P3: U7.9 (OUT3); also elsewhere on the board
/DB_2/PD_VBUS: C26.1, C28.1, C29.1, C30.1, C31.1, C32.1, U7.4 (VM), U7.11 (VM); also elsewhere on the board
/DB_2/SFOC_Mini_1/EN: R13.1, U7.22 (EN3), U7.24 (EN2), U7.26 (EN1)
/DB_2/SFOC_Mini_1/nFlt: R15.2, U7.18 (~FAULT); also elsewhere on the board
/DB_2/SFOC_Mini_1/nRes: R17.2, U7.16 (~RESET)
/DB_2/SFOC_Mini_1_EN: R13.2; also elsewhere on the board
/DB_2/SFOC_Mini_1_IN1: U7.27 (IN1); also elsewhere on the board
/DB_2/SFOC_Mini_1_IN2: U7.25 (IN2); also elsewhere on the board
/DB_2/SFOC_Mini_1_IN3: U7.23 (IN3); also elsewhere on the board
/DB_2/SFOC_Mini_Slp: R16.2, U7.17 (~SLEEP)
unnamed: C18.2, U7.1 (CP1)
unnamed: C18.1, U7.2 (CP2)
unnamed: C27.2, R15.1, R16.1, R17.1, U7.15 (V3P3OUT)
unnamed: C26.2, U7.3 (VCP)

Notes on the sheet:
VCC (8-60 V)
DRV8313 Motor Driver, SimpleFOC Mini 1.1 Implementation
3V3 Control
